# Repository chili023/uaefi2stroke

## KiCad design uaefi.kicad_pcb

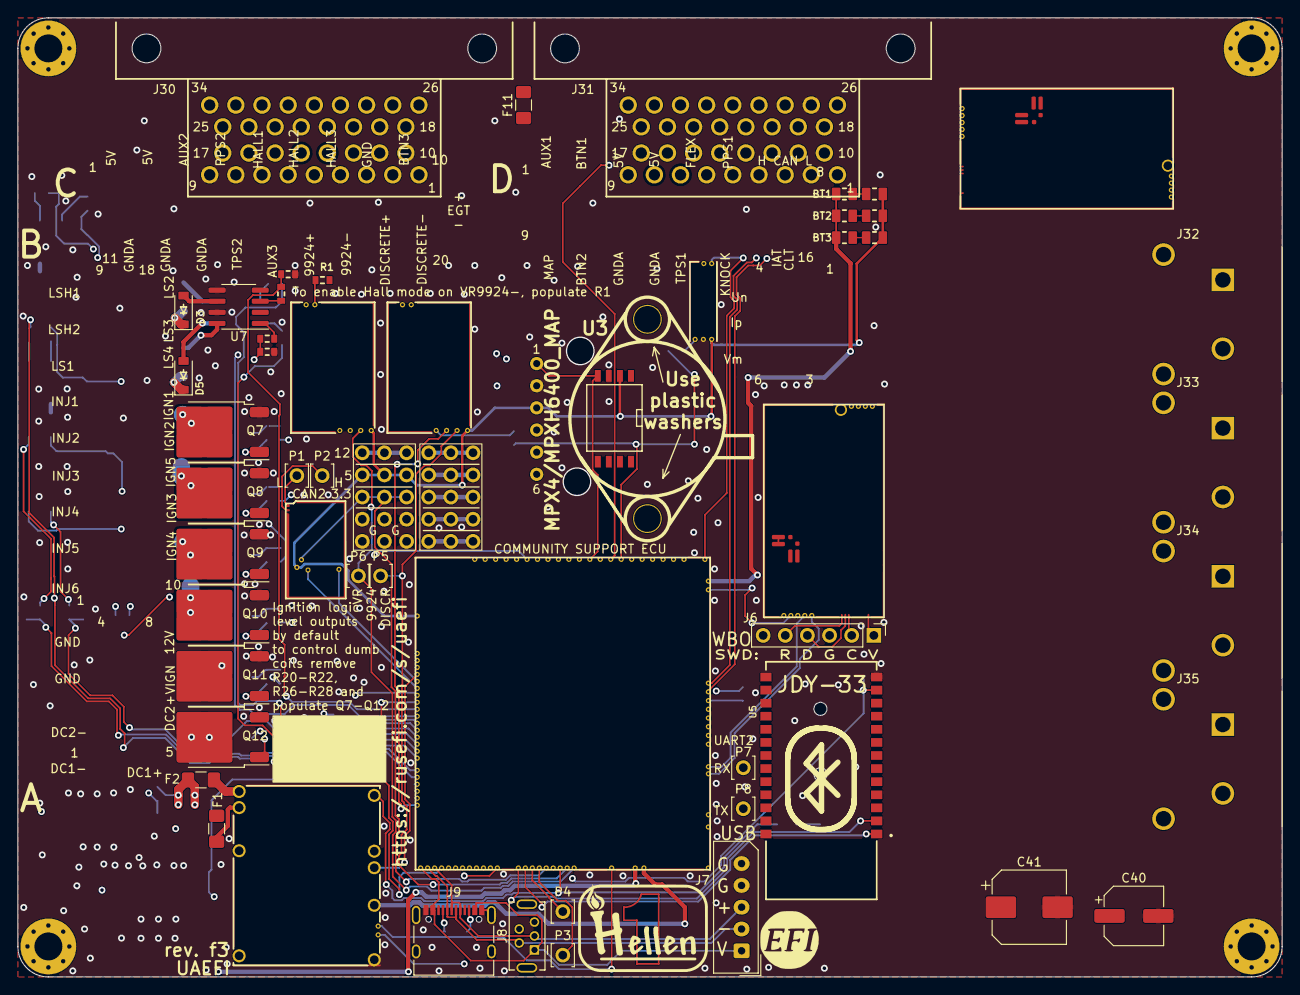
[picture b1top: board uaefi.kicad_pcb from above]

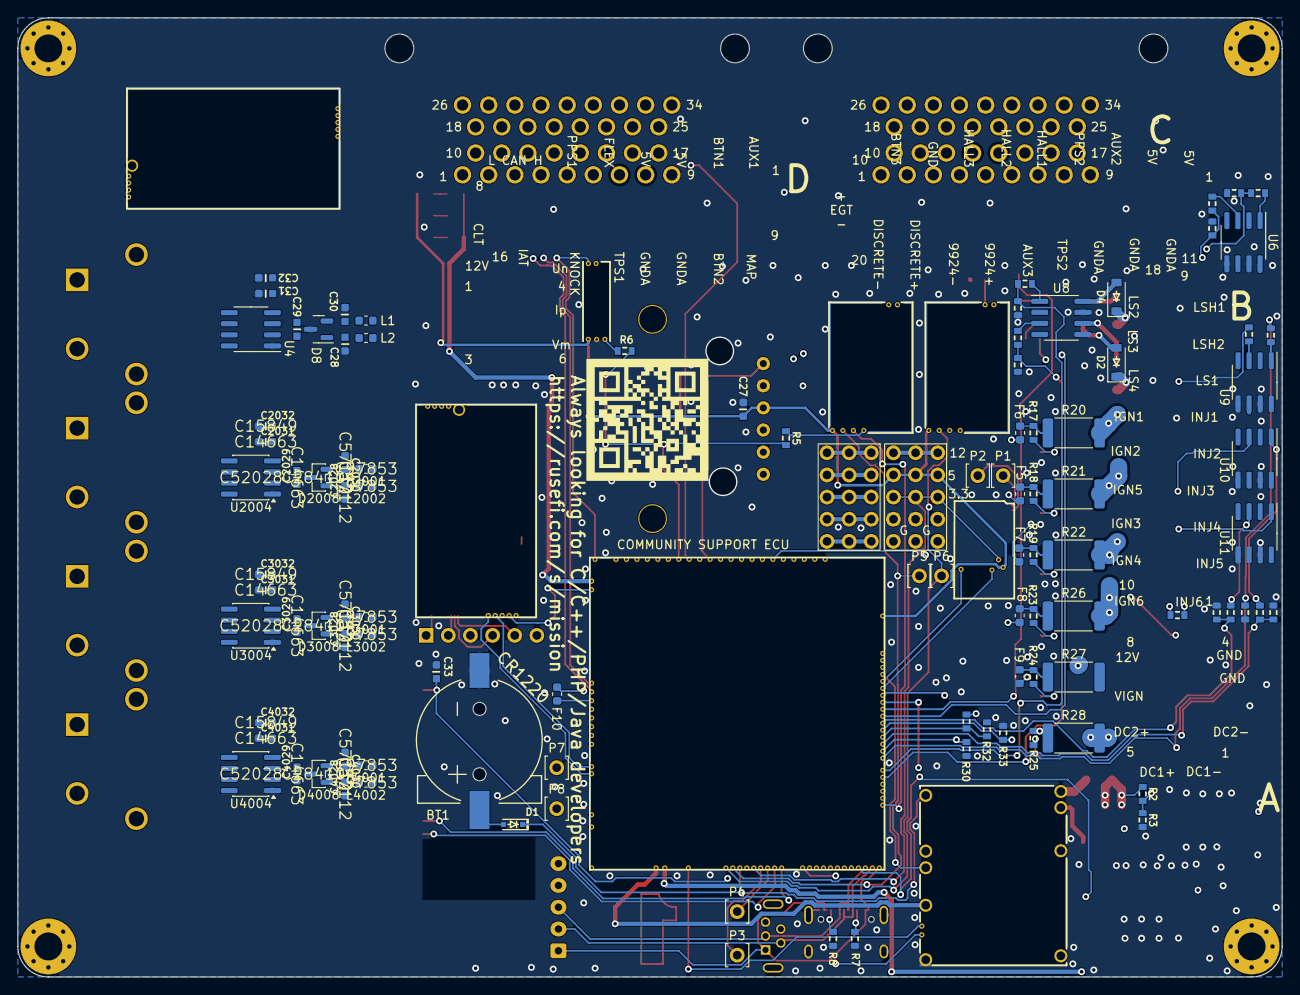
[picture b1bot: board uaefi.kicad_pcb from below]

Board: 4 copper layers, 145.0 x 110.0 mm, 152 parts (91 on the bottom side), 163 nets.

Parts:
BT1: CR1220; CR1220-2
C27, C29, C31, C33, C2029, C2031, C3029, C3031, C4029, C4031: 100n; C0603
C28, C30, C2028, C2030, C3028, C3030, C4028, C4030: 10n; C0603
C32, C2032, C3032, C4032: 1u; C0603
C40: 47uF 16V; CP_Elec_6.3x5.4
C41: 470uF 6.3V; CP_Elec_8x10
D1: 1N4148WS; SOD-323
D2, D3, D4, D5: B5819W; SOD-123
D8, D2008, D3008, D4008: NUP2105L; SOT-23
F1, F2: Fuse; Fuse_1206_3216Metric_Pad1.42x1.75mm_HandSolder
F5, F6, F7, F8, F9, F10: 50mA; Fuse_0603_1608Metric
F11: PTC 200mA hold; Fuse_1206_3216Metric_Pad1.42x1.75mm_HandSolder
G1: RUSEFI_LOGO; rusefi_logo
G2: LOGO
G3, G4: PROTO_AREA
H1, H2, H3, H4: M3; MountingHole_3.2mm_M3_Pad_Via
J6: Conn_01x06; PinHeader_1x06_P2.54mm_Vertical
J7: Conn_01x05_Male; Molex_SPOX_5267-05A_1x05_P2.50mm_Vertical
J8: USB_B_Mini; USB-MINI-B-VERTICAL
J9: USB_C
J30: TE 6437288-1 (A, keying 1); 6437288-2
J31: TE 6437288-2 (B, keying 2); 6437288-2
J32: EGT1 PCC-SMP-K; Omega_PCC-SMP-K
J33: EGT2 PCC-SMP-K; Omega_PCC-SMP-K
J34: EGT3 PCC-SMP-K; Omega_PCC-SMP-K
J35: EGT4 PCC-SMP-K; Omega_PCC-SMP-K
L1, L2, L2001, L2002, L3001, L3002, L4001, L4002: 470R@100MHz; L_0603_1608Metric
M1: Module-power_12and5V-0.3; power_12and5V
M2: Module-knock-0.2; knock
M3: Module-vr-discrete-0.5; vr-discrete
M4: Module-vr-max9924-0.1; vr-max9924
M5, M8: Module-wbo-0.6; wbo
M6: Module:mega-mcu100/0.3; mega-mcu100
M7: Module-can-0.1; can
P1, P2, P3, P4, P5, P6, P7, P8: Pad; PAD-TH
Q7, Q8, Q9, Q10, Q11, Q12: ISL9V3040D3ST; TO-252-2
R1, R4, R10, R11, R12, R13, R15, R16, R29, R30, R31, R32, R33, R34, R41, R42, R43, R44, R45, R46, R47, R48, R49, R50, R51: 4.7k; R0603
R2: 33k; R0603
R3: 6.8k; R0603
R5, R6: 0; R0603
R7, R8: 5.6k; R0603
R17, R18, R19, R23, R24, R25: 22; R0603
R20, R21, R22, R26, R27, R28: 0; R_2512_6332Metric
R35, R36, R37: 10k; R0805
R38, R40: DNP; R0805
R39: 4.7k; R0805
U3: MPX4/MPXH6400_MAP; MPX-4_MAP
U4, U2004, U3004, U4004: MAX31855KASA; SOIC-8_3.9x4.9mm_P1.27mm
U5: JDY-33
U6, U7, U8, U9, U10, U11: VNLD5160TR-E; SOIC-8_3.9x4.9mm_P1.27mm

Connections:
+3.3VA: C31.2, C32.2, C33.2, C41.1, C2031.2, C2032.2, C3031.2, C3032.2, C4031.2, C4032.2, G3.3, G3.8, G3.13, M6.N15 (V33_SWITCHABLE), M7.V2 (CAN_VIO), U4.4 (V_{CC}), U5.12 (3V3), U2004.4, U3004.4, U4004.4
+5V: C40.1, M1.E4 (V5), M6.N22 (VCC)
+5VA: C27.2, G3.4, G3.9, G3.14, M2.E1 (V5A), M3.E4 (V5_IN), M4.E4 (V5_IN), M5.W1 (V5_IN), M6.E1 (V5A_SWITCHABLE), M6.W2 (V5A_SWITCHABLE), M7.V1 (V5), M8.W1, R38.2, R39.2, R40.2, U3.3 (VCC)
+5VP: J30.4, J30.5, J31.2, M1.V4 (5VP), R1.1
+12V: F2.1, J30.1, R2.2
+12V_RAW: D2.1 (K), D3.1 (K), D4.1 (K), D5.1 (K), F2.2, F11.1, G3.5, G3.10, G3.15, J30.21, J31.29, M1.V1 (V12_PERM), M1.V3 (V12_RAW)
/1_WBO_Ip: J30.23, M5.E3 (LSU_Ip)
/2_WBO_Vm: J30.24, M5.E2 (LSU_Vm)
/3_WBO_Heater: J30.22, M5.E5 (LSU_Htr)
/5_WBO_Rtrim: J30.26, M5.E4 (LSU_Rtrim)
/6_WBO_Un: J30.25, M5.E1 (LSU_Un)
/12V_HALL: F11.2, J30.3, J31.1
/12V_KEY: F1.1, J30.2
/ADC3: M6.S15 (IN_KNOCK_(PA2)), R5.2, R6.2
/CAN+: J30.31, M5.W4 (CANH), M6.W11 (CANH), M8.W4
/CAN-: J30.32, M5.W3 (CANL), M6.W12 (CANL), M8.W3
/DC1_DIR: M6.E21 (OUT_PWM4_(PC8)), U3004.6
/DC1_PWM: M6.E20 (OUT_PWM3_(PC7)), U2004.6
/DC2_PWM: M6.E22 (OUT_PWM5_(PC9)), U4004.6
/EGT2+: J33.1, L2001.1
/EGT2-: J33.2, L2002.1
/EGT3+: J34.1, L3001.1
/EGT3-: J34.2, L3002.1
/EGT4+: J35.1, L4001.1
/EGT4-: J35.2, L4002.1
/EGT+: J32.1, L1.1
/EGT-: J32.2, L2.1
/EGT/SPI_CS: M6.N9 (SPI3_CS_(PA15)), U4.6 (~CS)
/IGN1: F6.2, M6.W10 (IGN1_(PC13))
/IGN2: F5.2, M6.W9 (IGN2_(PE5))
/IGN3: F7.2, M6.W8 (IGN3_(PE4))
/IGN4: F8.2, M6.W7 (IGN4_(PE3))
/IGN5: F9.2, M6.W6 (IGN5_(PE2))
/IGN6: F10.2, M6.W5 (IGN6_(PB8))
/INJ1: M6.E17 (OUT_INJ1_(PD3)), R29.2, R42.1
/INJ2: M6.E16 (OUT_INJ2_(PA9)), R30.2, R43.1
/INJ3: M6.E15 (OUT_INJ3_(PD11)), R31.2, R44.1
/INJ4: M6.E14 (OUT_INJ4_(PD10)), R32.2, R45.1
/INJ5: M6.E13 (OUT_INJ5_(PD2)), R33.2, R46.1
/INJ6: M6.E12 (OUT_INJ6_(PA8)), R34.2, R47.1
/INTERNAL_MAP: M6.S12 (IN_MAP2_(PC1)), U3.1 (VOUT)
/IN_AUX1: J31.15, M6.S11 (IN_O2S_/_CAN_WAKEUP_(PA0))
/IN_AUX2: J31.16, M6.S10 (IN_O2S2_(PA1))
/IN_AUX3: J31.11, M6.S7 (IN_AUX3_(PA7))
/IN_BUTTON1: J31.22, M6.S14 (IN_CRANK_(PB1)), R35.2, R38.1
/IN_BUTTON2: J31.28, M6.S16 (IN_CAM_(PA6)), R36.2, R39.1
/IN_BUTTON3: M6.S1 (IN_D4_(PE15)), R37.2, R40.1
/IN_CLT: J30.18, M6.S21 (IN_CLT_(PC2))
/IN_FLEX: J31.21, M6.S17 (IN_VSS_(PE11))
/IN_HALL1: J30.20, M6.S4 (IN_D1_(PE12))
/IN_HALL2: J31.19, M6.S3 (IN_D2_(PE13))
/IN_HALL3: J31.20, M6.S2 (IN_D3_(PE14))
/IN_IAT: J30.19, M6.S20 (IN_IAT_(PC3))
/IN_KNOCK: M2.E3 (OUT_KNOCK), R6.1
/IN_KNOCK_RAW: J30.34, M2.W1 (IN_KNOCK)
/IN_MAP: J31.14, M6.S13 (IN_MAP1_(PC0))
/IN_PPS1: J31.17, M6.S19 (IN_PPS_(PA3))
/IN_PPS2: J31.18, M6.S8 (IN_AUX2_(PC4/PE9))
/IN_TPS1: J30.17, M6.S18 (IN_TPS_(PA4))
/IN_TPS2: J31.13, M6.S9 (IN_AUX1_(PB0))
/IN_VIGN: F1.2, M1.V2 (IN_VIGN)
/IN_VMAIN: M6.S6 (IN_AUX4_(PC5)), R2.1, R3.2
/Ignition/OUT5: Q11.2 (C), R27.2
/Ignition/OUT6: Q12.2 (C), R28.2
/LS1: M6.E11 (OUT_INJ7_(PD15)), R10.2, R48.1
/LS2: M6.E10 (OUT_INJ8_(PD12)), R11.2, R49.1
/LS3: M6.E18 (OUT_PWM1_(PD13)), R12.2, R50.1
/LS4: M6.E19 (OUT_PWM2_(PC6)), R13.2, R51.1
/LS_HOT1: M6.W4 (IGN7_(PB9)), R16.1, R41.1
/LS_HOT2: M6.W3 (IGN8_(PE6)), R4.1, R15.1
/MISO3: M6.N11 (SPI3_MISO_(PC11)), U4.7 (SO), U2004.7, U3004.7, U4004.7
/OUT_IGN1: J30.13, Q7.2 (C), R20.2
/OUT_IGN2: J30.14, Q8.2 (C), R21.2
/OUT_IGN3: J31.7, Q9.2 (C), R22.2
/OUT_IGN4: J31.8, Q10.2 (C), R26.2
/OUT_INJ1: J30.11, U9.8 (D1)
/OUT_INJ2: J30.12, U9.6 (D2)
/OUT_INJ3: J31.5, U10.8 (D1)
/OUT_INJ4: J31.6, U10.6 (D2)
/OUT_LS1: D2.2 (A), J30.15, U7.8 (D1)
/OUT_LS2: D3.2 (A), J30.16, U7.6 (D2)
/OUT_LS3: D4.2 (A), J31.9, U8.8 (D1)
/OUT_LS4: D5.2 (A), J31.10, U8.6 (D2)
/OUT_LS_HOT1: J30.33, U6.6 (D2)
/OUT_LS_HOT2: J31.12, U6.8 (D1)
/PG_5VP: M1.E6 (PG_5VP), M6.N12 (SPI3_MOSI_(PC12))
/PWR_EN: M1.E5 (EN_5VP), M6.N20 (OUT_PWR_EN_(PE10))
/SCK3: M6.N10 (SPI3_SCK_(PC10)), U4.5 (SCK), U2004.5, U3004.5, U4004.5
/USB+: J7.3, J8.3 (D+), J9.A6 (D+), J9.B6 (D+), J30.28, M6.N3 (USBP_(PA12))
/USB-: J7.2, J8.2 (D-), J9.A7 (D-), J9.B7 (D-), J30.29, M6.N2 (USBM_(PA11))
/VBAT: D1.1 (K), M1.E1 (VBAT), M6.N17 (VBAT)
/VBUS: J7.1, J8.1 (VBUS), J9.A4 (VBUS), J9.A9 (VBUS), J9.B4 (VBUS), J9.B9 (VBUS), J30.27, M6.N1 (VBUS)
/VIGN: M1.E3 (VIGN), M6.E5 (IN_VIGN_(PA5))
/VREF1: M2.W2 (VREF), M6.S22 (VREF1)
/VR_DISCRETE: M3.E3 (OUT), M6.N18 (UART8_RX_(PE0)), P5.1
/VR_DISCRETE+: J31.23, M3.W2 (VR+)
/VR_DISCRETE-: J31.24, M3.W1 (VR-)
/VR_DISCRETE_A: M3.E2 (OUT_A), R5.1
/VR_DISCRETE_THR: M3.E1 (Thresh_IN), M6.E23 (OUT_PWM6_(PD14))
/VR_MAX9924: M4.E3 (OUT), M6.N19 (UART8_TX_(PE1)), P6.1
/VR_MAX9924+: J31.25, M4.W2 (VR+)
/VR_MAX9924-: J31.26, M4.W1 (VR-), R1.2
/WBO2_Heater: J31.30, M8.E5
/WBO2_Ip: J31.31, M8.E3
/WBO2_Rtrim: J31.34, M8.E4
/WBO2_SEL2: M8.J2, M8.J_VCC2
/WBO2_Un: J31.33, M8.E1
/WBO2_Vm: J31.32, M8.E2
GND: BT1.2 (-), C27.1, C28.1, C30.1, C31.1, C32.1, C33.1, C40.2, C41.2, C2028.1, C2030.1, C2031.1, C2032.1, C3028.1, C3030.1, C3031.1, C3032.1, C4028.1, C4030.1, C4031.1, C4032.1, D8.3 (A), D2008.3, D3008.3, D4008.3, G3.1, G3.2, G3.6, G3.7, G3.11, G3.12, J6.3, J7.4, J7.5, J8.5 (GND), J8.6 (Shield), J9.A1 (GND), J9.A12 (GND), J9.B1 (GND), J9.B12 (GND), J9.S1 (SHIELD), J30.8, J30.9, J30.10, J30.30, J31.4, J31.27, M1.S1 (GND), M2.E2 (GND), M3.G (GND), M4.G (GND), M5.G (GND), M6.G (GND), M7.E1 (GND), M8.G, Q7.3 (E), Q8.3 (E), Q9.3 (E), Q10.3 (E), Q11.3 (E), Q12.3 (E), R3.1, R7.1, R8.1, R10.1, R11.1, R12.1, R13.1, R15.2, R16.2, R29.1, R30.1, R31.1, R32.1, R33.1, R34.1, U3.2 (GND), U4.1 (GND), U5.13 (GND), U6.5 (S2), U6.7 (S1), U7.5 (S2), U7.7 (S1), U8.5 (S2), U8.7 (S1), U9.5 (S2), U9.7 (S1), U10.5 (S2), U10.7 (S1), U11.5 (S2), U11.7 (S1), U2004.1, U3004.1, U4004.1
GNDA: J30.6, J30.7, J31.3, M6.W1 (GNDA), R35.1, R36.1, R37.1
unnamed: BT1.1 (+), D1.2 (A)
unnamed: F5.1, R18.2, R21.1
unnamed: F6.1, R17.2, R20.1
unnamed: F7.1, R19.2, R22.1
unnamed: F8.1, R23.2, R26.1
unnamed: F9.1, R24.2, R27.1
unnamed: F10.1, R25.2, R28.1
unnamed: G4.1, G4.6, G4.11
unnamed: G4.5, G4.10, G4.15
unnamed: G4.2, G4.7, G4.12
unnamed: G4.3, G4.8, G4.13
unnamed: G4.4, G4.9, G4.14
unnamed: J6.1, M5.W8 (V33_OUT)
unnamed: J6.2, M5.W7 (SWCLK)
unnamed: J6.4, M5.W6 (SWDIO)
unnamed: J6.5, M5.W5 (nReset)
unnamed: J9.A5 (CC1), R7.2
unnamed: J9.B5 (CC2), R8.2
unnamed: M5.J1 (SEL1), M5.J_GND1 (PULL_DOWN1)
unnamed: M6.N14a (LED_GREEN), P4.1
unnamed: M6.N14b (LED_YELLOW), P3.1
unnamed: M6.E6 (SPI2_CS_/_CAN2_RX_(PB12)), M7.V6 (CAN_RX)
unnamed: M6.E7 (SPI2_SCK_/_CAN2_TX_(PB13)), M7.V5 (CAN_TX)
unnamed: M6.N14 (UART2_RX_(PD6)), P7.1, U5.1 (TXD)
unnamed: M6.N13 (UART2_TX_(PD5)), P8.1, U5.2 (RXD)
unnamed: M7.S2 (CANH), P2.1
unnamed: M7.S1 (CANL), P1.1
unnamed: Q7.1 (G), R17.1
unnamed: Q8.1 (G), R18.1
unnamed: Q9.1 (G), R19.1
unnamed: Q10.1 (G), R23.1
unnamed: Q11.1 (G), R24.1
unnamed: Q12.1 (G), R25.1
unnamed: C29.2, C30.2, D8.2 (K), L1.2, U4.3 (T+)
unnamed: C28.2, C29.1, D8.1 (K), L2.2, U4.2 (T-)
unnamed: R4.2, U6.1 (IN1)
unnamed: R41.2, U6.3 (IN2)
unnamed: R48.2, U7.1 (IN1)
unnamed: R49.2, U7.3 (IN2)
unnamed: R50.2, U8.1 (IN1)
unnamed: R51.2, U8.3 (IN2)
unnamed: R42.2, U9.1 (IN1)
unnamed: R43.2, U9.3 (IN2)
unnamed: R44.2, U10.1 (IN1)
unnamed: R45.2, U10.3 (IN2)
unnamed: R46.2, U11.1 (IN1)
unnamed: R47.2, U11.3 (IN2)
unnamed: C2029.2, C2030.2, D2008.2, L2001.2, U2004.3
unnamed: C2028.2, C2029.1, D2008.1, L2002.2, U2004.2
unnamed: C3029.2, C3030.2, D3008.2, L3001.2, U3004.3
unnamed: C3028.2, C3029.1, D3008.1, L3002.2, U3004.2
unnamed: C4029.2, C4030.2, D4008.2, L4001.2, U4004.3
unnamed: C4028.2, C4029.1, D4008.1, L4002.2, U4004.2
